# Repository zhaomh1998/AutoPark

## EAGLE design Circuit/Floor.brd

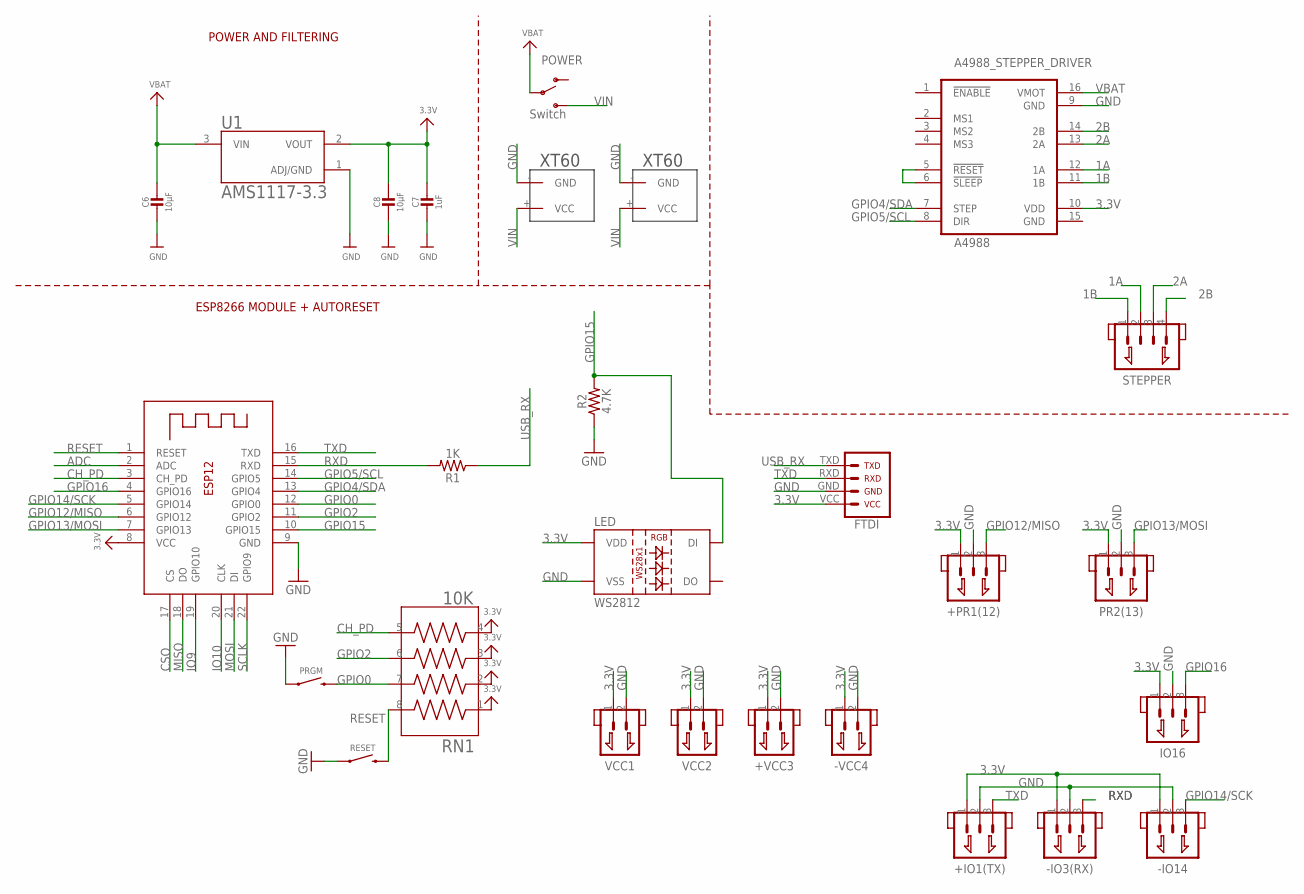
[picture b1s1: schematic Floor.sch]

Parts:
+IO1(TX): XH_2.54_3P; XH2.54_3P
+PR1(12): XH_2.54_3P; XH2.54_3P
+VCC3: XH_2.54_2P; XH2.54_2P
-IO3(RX), -IO14: XH_2.54_3P; XH2.54_3P
-VCC4: XH_2.54_2P; XH2.54_2P
A4988: A4988_STEPPER_DRIVER; A4988
C6, C8: 10µF; MICROBUILDER__0805
C7: 1uF; MICROBUILDER__0603
IO16: XH_2.54_3P; XH2.54_3P
LED: WS2812; LED-TRICOLOR-5050-IC
POWER: Switch; SWITCH_SPDT_PTH_11.6X4.0MM
PR2(13): XH_2.54_3P; XH2.54_3P
PRGM: PUSHBUTTON; TACTILE_SWITCH_SMD_6.0X3.5MM
R1: 1K; 1206
R2: 4.7K; 1206
RESET: PUSHBUTTON; TACTILE_SWITCH_SMD_6.0X3.5MM
RN1: 10K; RESCAF80P320X160X60-8N
STEPPER: XH_2.54_4P; XH2.54_4P
U1: AMS1117-3.3; SOT229P700X180-4N
U$7, U$9: XT60
U$11: FTDI; 1X06
VCC1, VCC2: XH_2.54_2P; XH2.54_2P
X2: ESP-12; MICROBUILDER_ESP-12E

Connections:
1A: A4988.12 (1A), STEPPER.2
1B: A4988.11 (1B), STEPPER.1
2A: A4988.13 (2A), STEPPER.3
2B: A4988.14 (2B), STEPPER.4
3.3V: +IO1(TX).1, +PR1(12).1, +VCC3.1, -IO3(RX).1, -IO14.1, -VCC4.1, A4988.10 (VDD), C7.1, C8.1, IO16.1, LED.VDD, PR2(13).1, RN1.1, RN1.2, RN1.3, RN1.4, U1.2 (VOUT), U$11.VCC, VCC1.1, VCC2.1, X2.8 (VCC)
ADC: X2.2 (ADC)
CH_PD: RN1.5, X2.3 (CH_PD)
CSO: X2.17 (CS)
GND: +IO1(TX).2, +PR1(12).2, +VCC3.2, -IO3(RX).2, -IO14.2, -VCC4.2, A4988.9 (GND), A4988.15 (GND), C6.2, C7.2, C8.2, IO16.2, LED.VSS, PR2(13).2, PRGM.1, R2.1, RESET.1, U1.1 (ADJ/GND), U$7.- (GND), U$9.- (GND), U$11.GND, VCC1.2, VCC2.2, X2.9 (GND)
GPIO0: PRGM.2, RN1.7, X2.12 (GPIO0)
GPIO2: RN1.6, X2.11 (GPIO2)
GPIO4/SDA: A4988.7 (STEP), X2.13 (GPIO4)
GPIO5/SCL: A4988.8 (DIR), X2.14 (GPIO5)
GPIO12/MISO: +PR1(12).3, X2.6 (GPIO12)
GPIO13/MOSI: PR2(13).3, X2.7 (GPIO13)
GPIO14/SCK: -IO14.3, X2.5 (GPIO14)
GPIO15: LED.DIN (DI), R2.2, X2.10 (GPIO15)
GPIO16: IO16.3, X2.4 (GPIO16)
IO9: X2.19 (GPIO10)
IO10: X2.20 (CLK)
MISO: X2.18 (DO)
MOSI: X2.21 (DI)
unnamed: A4988.5 (!RESET), A4988.6 (!SLEEP)
RESET: RESET.2, RN1.8, X2.1 (RESET)
RXD: -IO3(RX).3, R1.2, X2.15 (RXD)
SCLK: X2.22 (GPIO9)
TXD: +IO1(TX).3, U$11.RXD, X2.16 (TXD)
USB_RX: R1.1, U$11.TXD
VBAT: A4988.16 (VMOT), C6.1, POWER.2, U1.3 (VIN)
VIN: POWER.3 (S), U$7.+ (VCC), U$9.+ (VCC)

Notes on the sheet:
POWER AND FILTERING
ESP8266 MODULE + AUTORESET

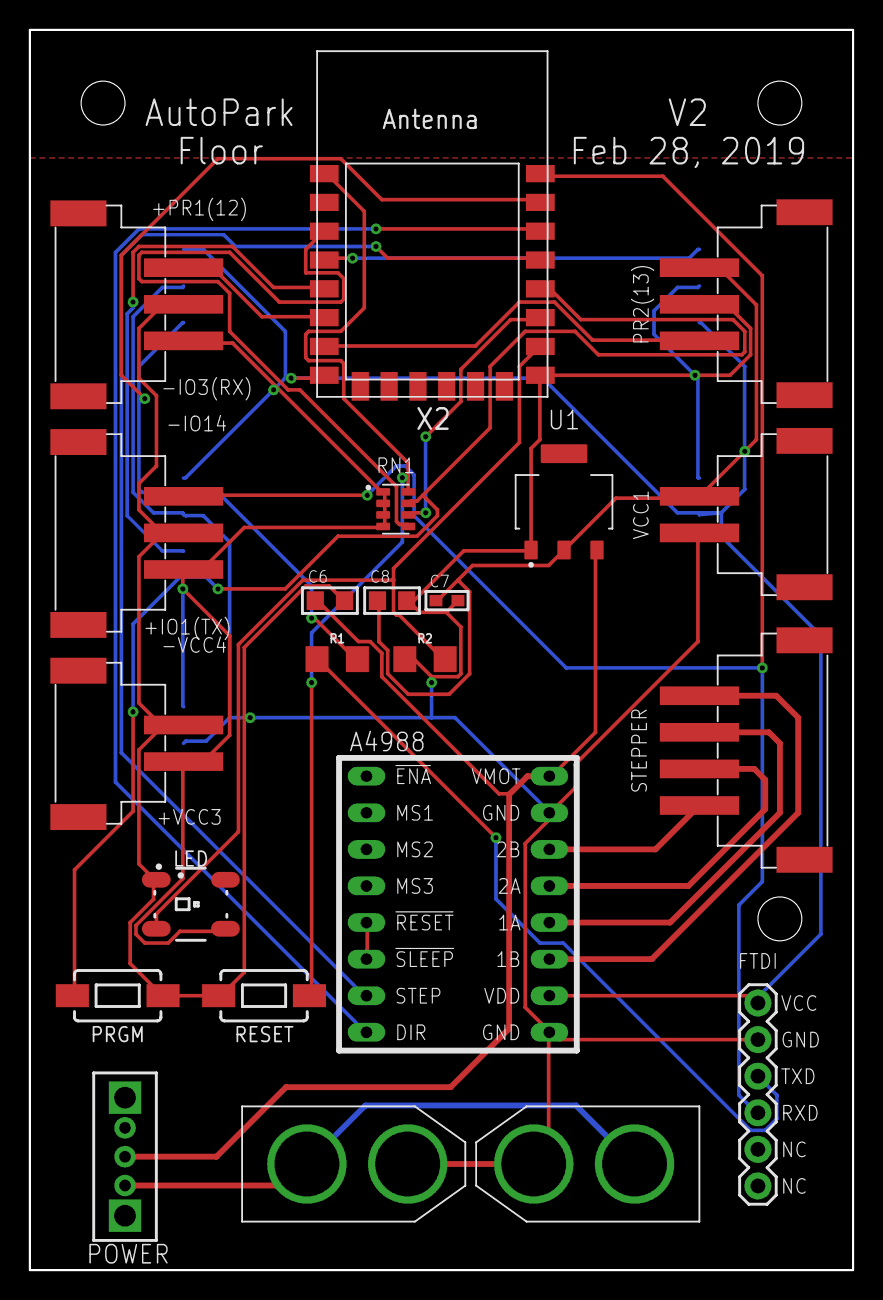
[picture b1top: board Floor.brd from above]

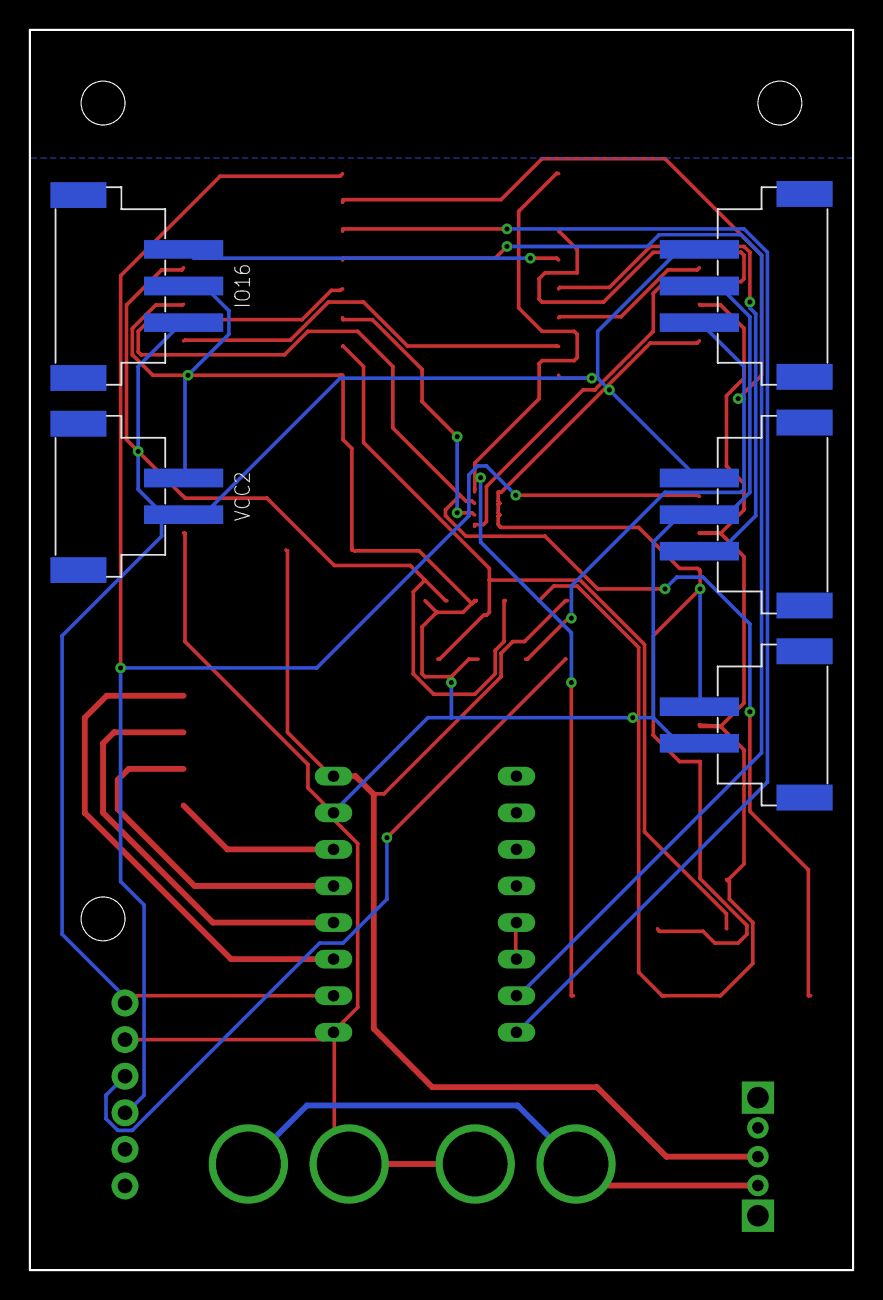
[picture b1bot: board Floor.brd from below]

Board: 2 copper layers, 57.2 x 86.1 mm, 27 parts (5 on the bottom side), 23 nets.

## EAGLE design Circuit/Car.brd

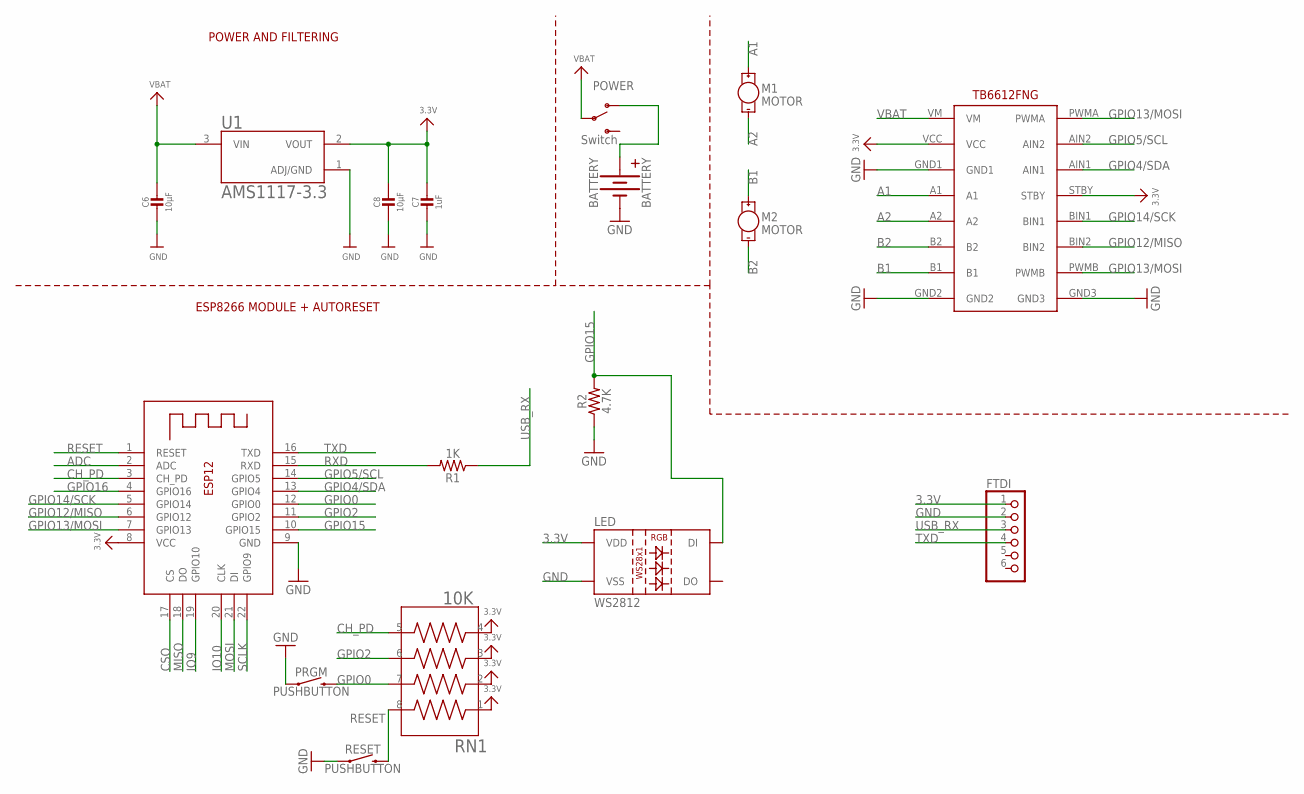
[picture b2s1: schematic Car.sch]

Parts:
BATTERY: BATTERY; BATTERY-AA-KIT
C6, C8: 10µF; MICROBUILDER__0805
C7: 1uF; MICROBUILDER__0603
FTDI: PINHD-1X6; 1X06
LED: WS2812; LED-TRICOLOR-5050-IC
M1, M2: MOTOR; 1X02_PLUS_MINUS
POWER: Switch; SWITCH_SPDT_PTH_11.6X4.0MM
PRGM: PUSHBUTTON; TACTILE_SWITCH_SMD_6.0X3.5MM
R1: 1K; 1206
R2: 4.7K; 1206
RESET: PUSHBUTTON; TACTILE_SWITCH_SMD_6.0X3.5MM
RN1: 10K; RESCAF80P320X160X60-8N
TB1: TB6612FNG
U1: AMS1117-3.3; SOT229P700X180-4N
X2: ESP-12; ESP-12E

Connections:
3.3V: C7.1, C8.1, FTDI.1, LED.VDD, RN1.1, RN1.2, RN1.3, RN1.4, TB1.STBY, TB1.VCC, U1.2 (VOUT), X2.8 (VCC)
A1: M1.+, TB1.A1
A2: M1.-, TB1.A2
ADC: X2.2 (ADC)
B1: M2.+, TB1.B1
B2: M2.-, TB1.B2
CH_PD: RN1.5, X2.3 (CH_PD)
CSO: X2.17 (CS)
GND: BATTERY.GND (-), C6.2, C7.2, C8.2, FTDI.2, LED.VSS, PRGM.1, R2.1, RESET.1, TB1.GND1, TB1.GND2, TB1.GND3, U1.1 (ADJ/GND), X2.9 (GND)
GPIO0: PRGM.2, RN1.7, X2.12 (GPIO0)
GPIO2: RN1.6, X2.11 (GPIO2)
GPIO4/SDA: TB1.AIN1, X2.13 (GPIO4)
GPIO5/SCL: TB1.AIN2, X2.14 (GPIO5)
GPIO12/MISO: TB1.BIN2, X2.6 (GPIO12)
GPIO13/MOSI: TB1.PWMA, TB1.PWMB, X2.7 (GPIO13)
GPIO14/SCK: TB1.BIN1, X2.5 (GPIO14)
GPIO15: LED.DIN (DI), R2.2, X2.10 (GPIO15)
GPIO16: X2.4 (GPIO16)
IO9: X2.19 (GPIO10)
IO10: X2.20 (CLK)
MISO: X2.18 (DO)
MOSI: X2.21 (DI)
unnamed: BATTERY.PWR (+), POWER.1 (O)
RESET: RESET.2, RN1.8, X2.1 (RESET)
RXD: R1.2, X2.15 (RXD)
SCLK: X2.22 (GPIO9)
TXD: FTDI.4, X2.16 (TXD)
USB_RX: FTDI.3, R1.1
VBAT: C6.1, POWER.2, TB1.VM, U1.3 (VIN)

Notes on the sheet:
POWER AND FILTERING
ESP8266 MODULE + AUTORESET

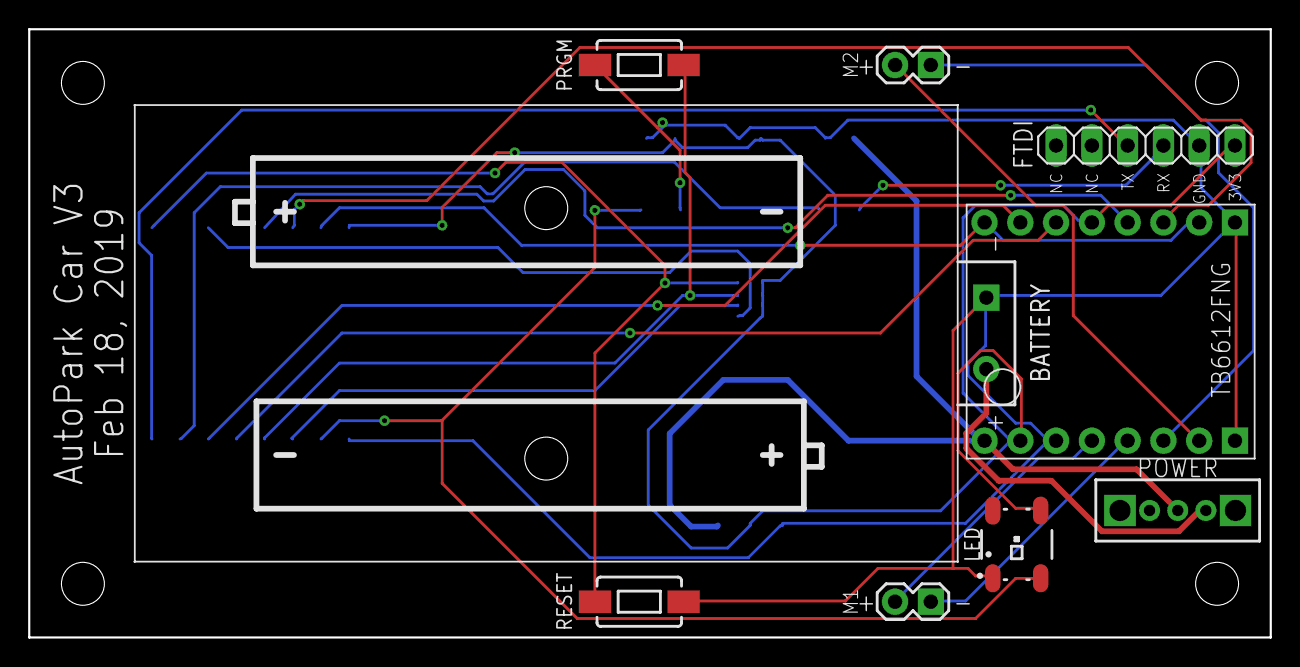
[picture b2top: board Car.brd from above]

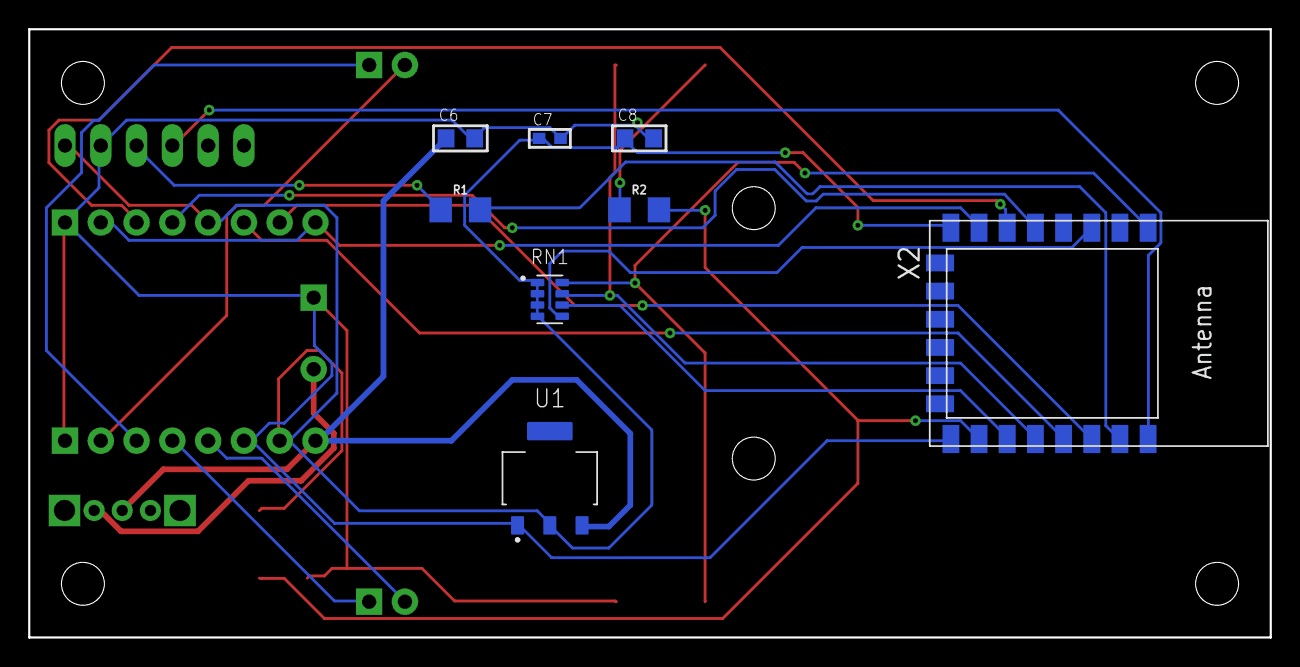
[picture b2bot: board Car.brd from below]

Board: 2 copper layers, 88.1 x 43.2 mm, 17 parts (8 on the bottom side), 21 nets.

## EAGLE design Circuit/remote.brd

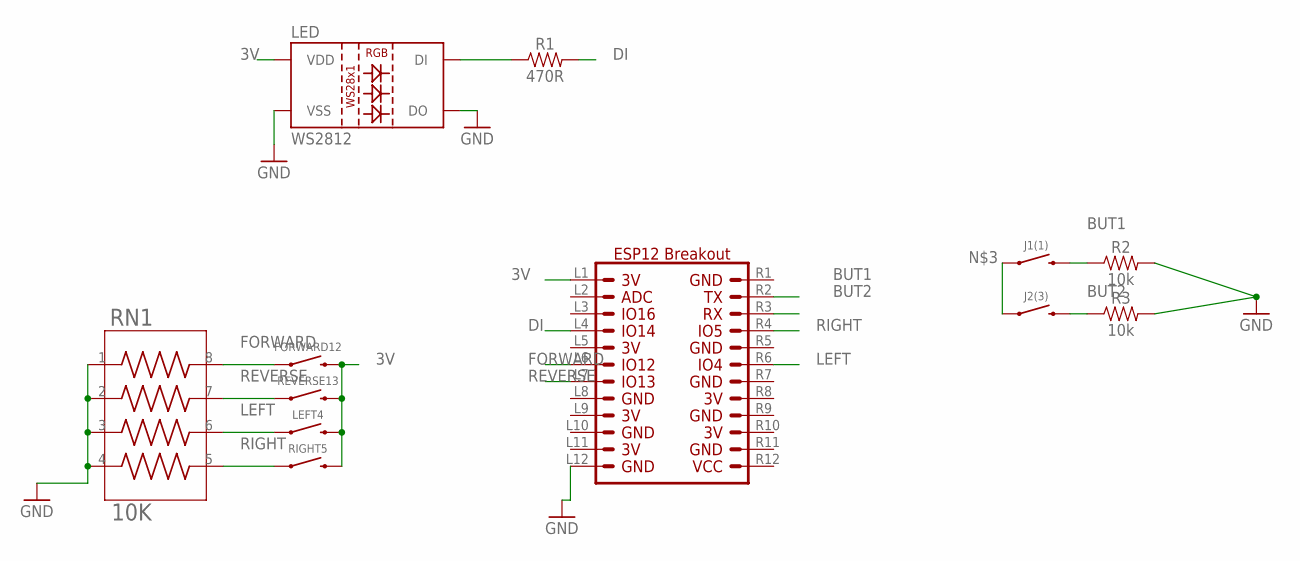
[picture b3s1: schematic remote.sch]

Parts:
FORWARD12: PUSHBUTTON_THD; TACTILE_SWITCH_PTH_6.0MM
J1(1), J2(3): PUSHBUTTON_THD; TACTILE_SWITCH_PTH_6.0MM
LED: WS2812; LED-TRICOLOR-5050-IC
LEFT4: PUSHBUTTON_THD; TACTILE_SWITCH_PTH_6.0MM
R1: 470R; SPARKFUN-RESISTORS_1206
R2, R3: 10k; SPARKFUN-RESISTORS_1206
REVERSE13: PUSHBUTTON_THD; TACTILE_SWITCH_PTH_6.0MM
RIGHT5: PUSHBUTTON_THD; TACTILE_SWITCH_PTH_6.0MM
RN1: 10K; RESCAF80P320X160X60-8N
U$1: ESP12_BREAKOUT; ESP12_BREAKOUT_CONN

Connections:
3V: FORWARD12.3 (2), LED.VDD, LEFT4.3 (2), REVERSE13.3 (2), RIGHT5.3 (2), U$1.L1
BUT1: J1(1).3 (2), R2.1, U$1.R2
BUT2: J2(3).3 (2), R3.1, U$1.R3
DI: R1.2, U$1.L4
FORWARD: FORWARD12.1, RN1.8, U$1.L6
GND: LED.DOUT (DO), LED.VSS, R2.2, R3.2, RN1.1, RN1.2, RN1.3, RN1.4, U$1.L12
LEFT: LEFT4.1, RN1.6, U$1.R6
unnamed: J1(1).1, J2(3).1
unnamed: LED.DIN (DI), R1.1
REVERSE: REVERSE13.1, RN1.7, U$1.L7
RIGHT: RIGHT5.1, RN1.5, U$1.R4

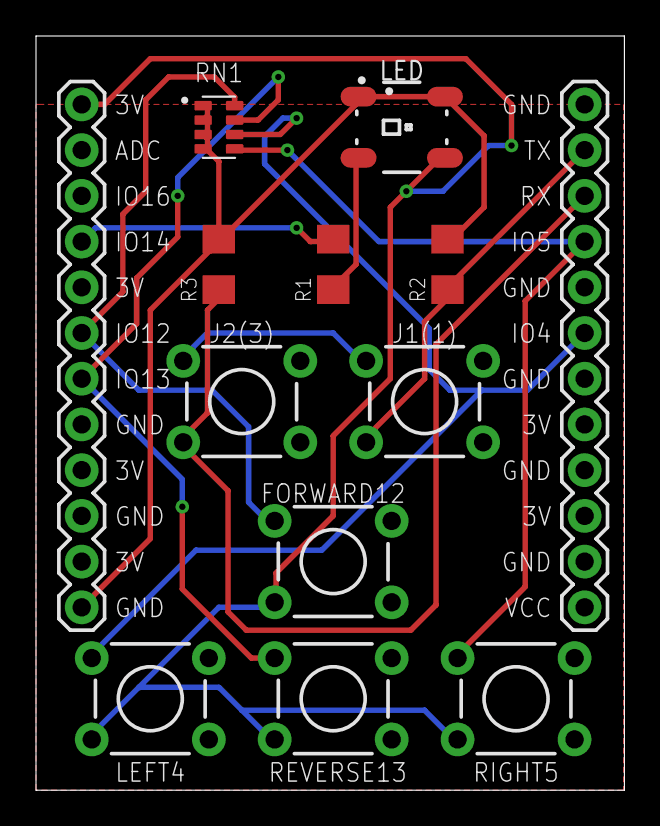
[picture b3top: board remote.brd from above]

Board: 2 copper layers, 32.7 x 41.9 mm, 12 parts (0 on the bottom side), 11 nets.

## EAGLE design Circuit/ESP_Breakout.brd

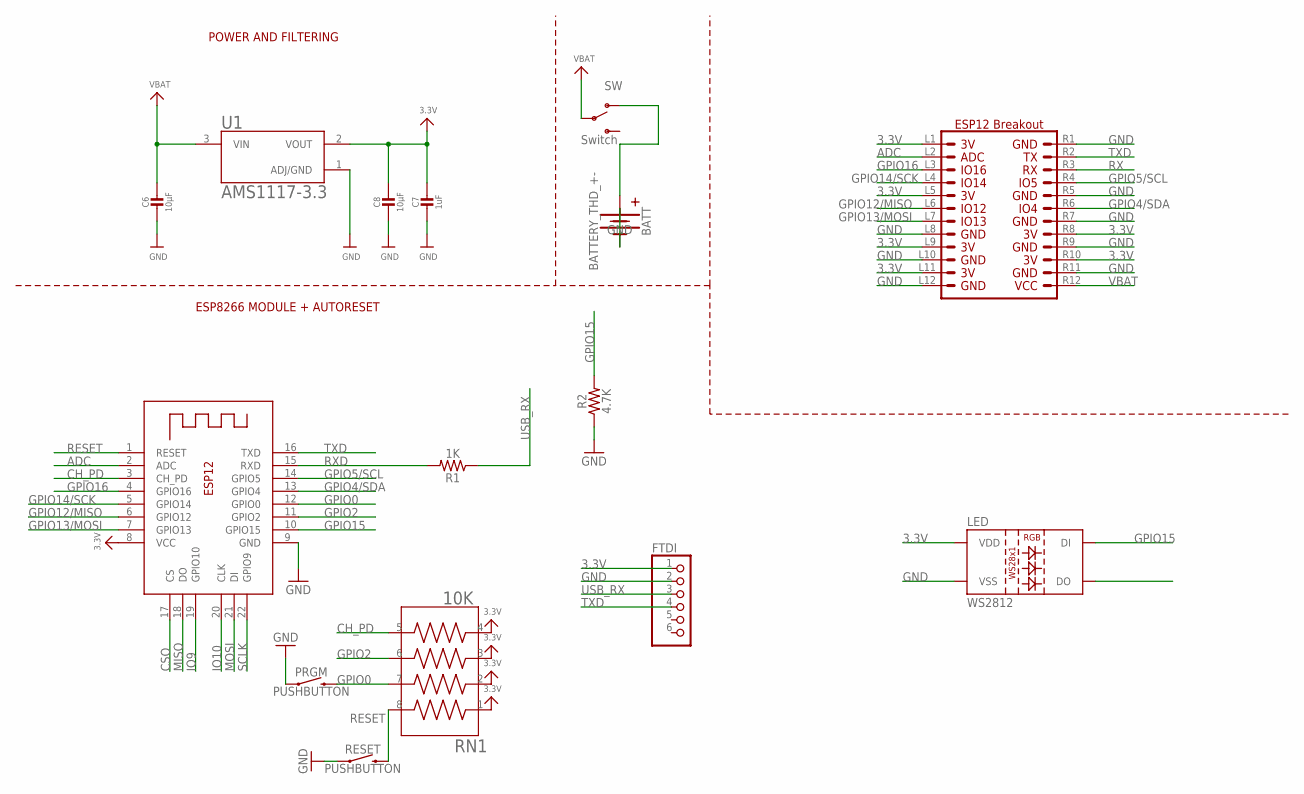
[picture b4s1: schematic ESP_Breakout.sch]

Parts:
BATT: BATTERY_THD_+-; 1X02_PLUS_MINUS
C6, C8: 10µF; MICROBUILDER__0805
C7: 1uF; MICROBUILDER__0603
FTDI: PINHD-1X6; 1X06
LED: WS2812; LED-TRICOLOR-5050-IC
PRGM: PUSHBUTTON; TACTILE_SWITCH_SMD_6.0X3.5MM
R1: 1K; 1206
R2: 4.7K; 1206
RESET: PUSHBUTTON; TACTILE_SWITCH_SMD_6.0X3.5MM
RN1: 10K; RESCAF80P320X160X60-8N
SW: Switch; SWITCH_SPDT_PTH_11.6X4.0MM
U1: AMS1117-3.3; SOT229P700X180-4N
U$7: ESP12_BREAKOUT; ESP12_BREAKOUT_CONN
X2: ESP-12; ESP-12E

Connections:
3.3V: C7.1, C8.1, FTDI.1, LED.VDD, RN1.1, RN1.2, RN1.3, RN1.4, U1.2 (VOUT), U$7.L1, U$7.L5, U$7.L9, U$7.L11, U$7.R8, U$7.R10, X2.8 (VCC)
ADC: U$7.L2, X2.2 (ADC)
CH_PD: RN1.5, X2.3 (CH_PD)
CSO: X2.17 (CS)
GND: BATT.-, C6.2, C7.2, C8.2, FTDI.2, LED.VSS, PRGM.1, R2.1, RESET.1, U1.1 (ADJ/GND), U$7.L8, U$7.L10, U$7.L12, U$7.R1, U$7.R5, U$7.R7, U$7.R9, U$7.R11, X2.9 (GND)
GPIO0: PRGM.2, RN1.7, X2.12 (GPIO0)
GPIO2: RN1.6, X2.11 (GPIO2)
GPIO4/SDA: U$7.R6, X2.13 (GPIO4)
GPIO5/SCL: U$7.R4, X2.14 (GPIO5)
GPIO12/MISO: U$7.L6, X2.6 (GPIO12)
GPIO13/MOSI: U$7.L7, X2.7 (GPIO13)
GPIO14/SCK: U$7.L4, X2.5 (GPIO14)
GPIO15: LED.DIN (DI), R2.2, X2.10 (GPIO15)
GPIO16: U$7.L3, X2.4 (GPIO16)
IO9: X2.19 (GPIO10)
IO10: X2.20 (CLK)
MISO: X2.18 (DO)
MOSI: X2.21 (DI)
unnamed: BATT.+, SW.1 (O)
RESET: RESET.2, RN1.8, X2.1 (RESET)
RX: U$7.R3
RXD: R1.2, X2.15 (RXD)
SCLK: X2.22 (GPIO9)
TXD: FTDI.4, U$7.R2, X2.16 (TXD)
USB_RX: FTDI.3, R1.1
VBAT: C6.1, SW.2, U1.3 (VIN), U$7.R12

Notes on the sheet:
POWER AND FILTERING
ESP8266 MODULE + AUTORESET

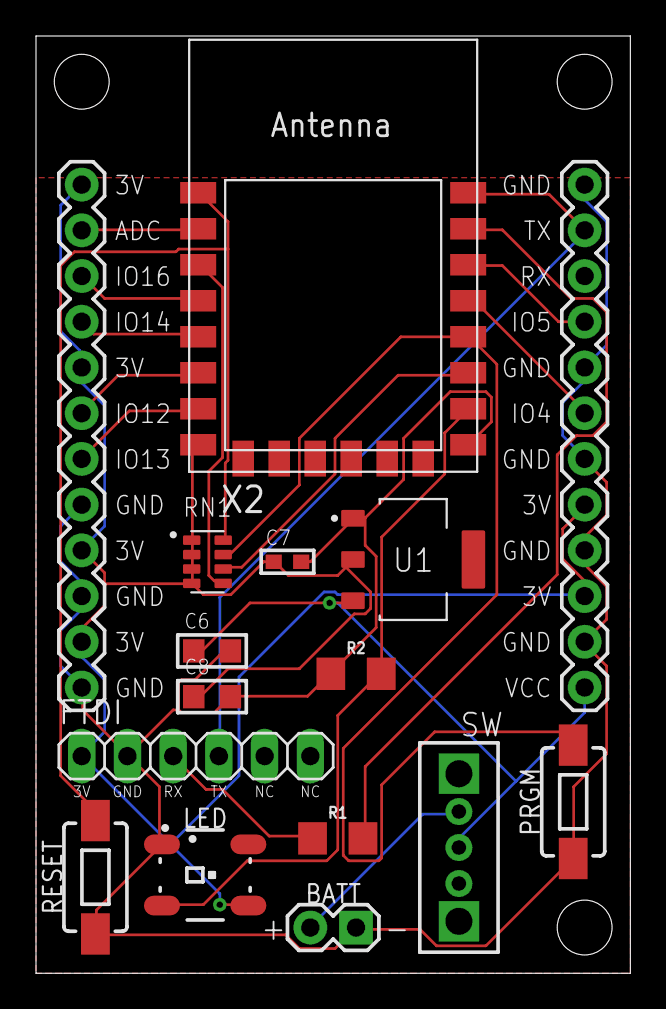
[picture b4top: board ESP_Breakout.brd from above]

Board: 2 copper layers, 33.0 x 52.1 mm, 15 parts (0 on the bottom side), 19 nets.

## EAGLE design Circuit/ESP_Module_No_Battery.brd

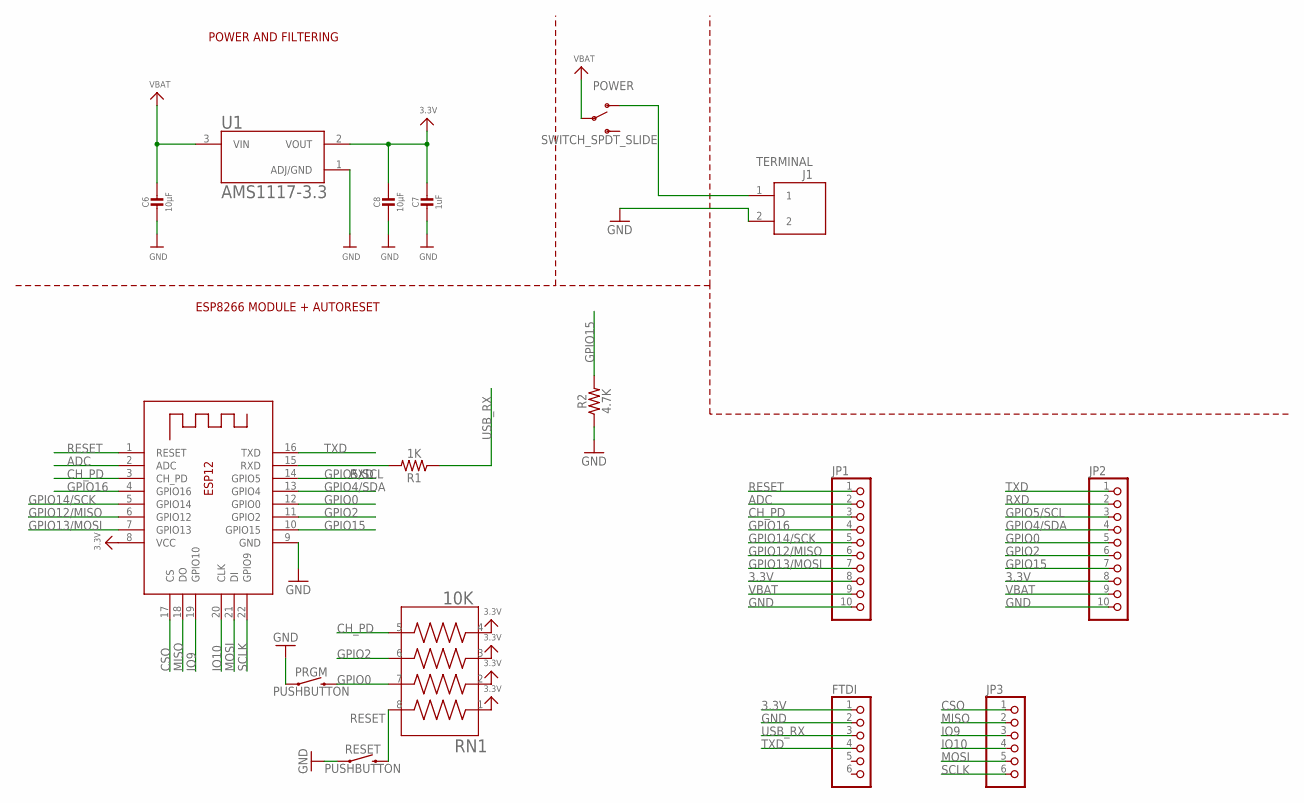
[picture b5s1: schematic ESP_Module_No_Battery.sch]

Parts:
C6, C8: 10µF; 0805-NO
C7: 1uF; 0603-NO
FTDI: PINHD-1X6; 1X06
J1: TERMINAL; ED555/2DS
JP1, JP2: PINHD-1X10; 1X10
JP3: PINHD-1X6; 1X06
POWER: SWITCH_SPDT_SLIDE; SWITCH_SPDT_PTH_11.6X4.0MM
PRGM: PUSHBUTTON; TACTILE_SWITCH_SMD_6.0X3.5MM
R1: 1K; 1206
R2: 4.7K; 1206
RESET: PUSHBUTTON; TACTILE_SWITCH_SMD_6.0X3.5MM
RN1: 10K; RESCAF80P320X160X60-8N
U1: AMS1117-3.3; SOT229P700X180-4N
X2: ESP-12; ESP-12E

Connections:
3.3V: C7.1, C8.1, FTDI.1, JP1.8, JP2.8, RN1.1, RN1.2, RN1.3, RN1.4, U1.2 (VOUT), X2.8 (VCC)
ADC: JP1.2, X2.2 (ADC)
CH_PD: JP1.3, RN1.5, X2.3 (CH_PD)
CSO: JP3.1, X2.17 (CS)
GND: C6.2, C7.2, C8.2, FTDI.2, J1.2, JP1.10, JP2.10, PRGM.1, R2.1, RESET.1, U1.1 (ADJ/GND), X2.9 (GND)
GPIO0: JP2.5, PRGM.2, RN1.7, X2.12 (GPIO0)
GPIO2: JP2.6, RN1.6, X2.11 (GPIO2)
GPIO4/SDA: JP2.4, X2.13 (GPIO4)
GPIO5/SCL: JP2.3, X2.14 (GPIO5)
GPIO12/MISO: JP1.6, X2.6 (GPIO12)
GPIO13/MOSI: JP1.7, X2.7 (GPIO13)
GPIO14/SCK: JP1.5, X2.5 (GPIO14)
GPIO15: JP2.7, R2.2, X2.10 (GPIO15)
GPIO16: JP1.4, X2.4 (GPIO16)
IO9: JP3.3, X2.19 (GPIO10)
IO10: JP3.4, X2.20 (CLK)
MISO: JP3.2, X2.18 (DO)
MOSI: JP3.5, X2.21 (DI)
unnamed: J1.1, POWER.1 (O)
RESET: JP1.1, RESET.2, RN1.8, X2.1 (RESET)
RXD: JP2.2, R1.2, X2.15 (RXD)
SCLK: JP3.6, X2.22 (GPIO9)
TXD: FTDI.4, JP2.1, X2.16 (TXD)
USB_RX: FTDI.3, R1.1
VBAT: C6.1, JP1.9, JP2.9, POWER.2, U1.3 (VIN)

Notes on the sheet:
POWER AND FILTERING
ESP8266 MODULE + AUTORESET

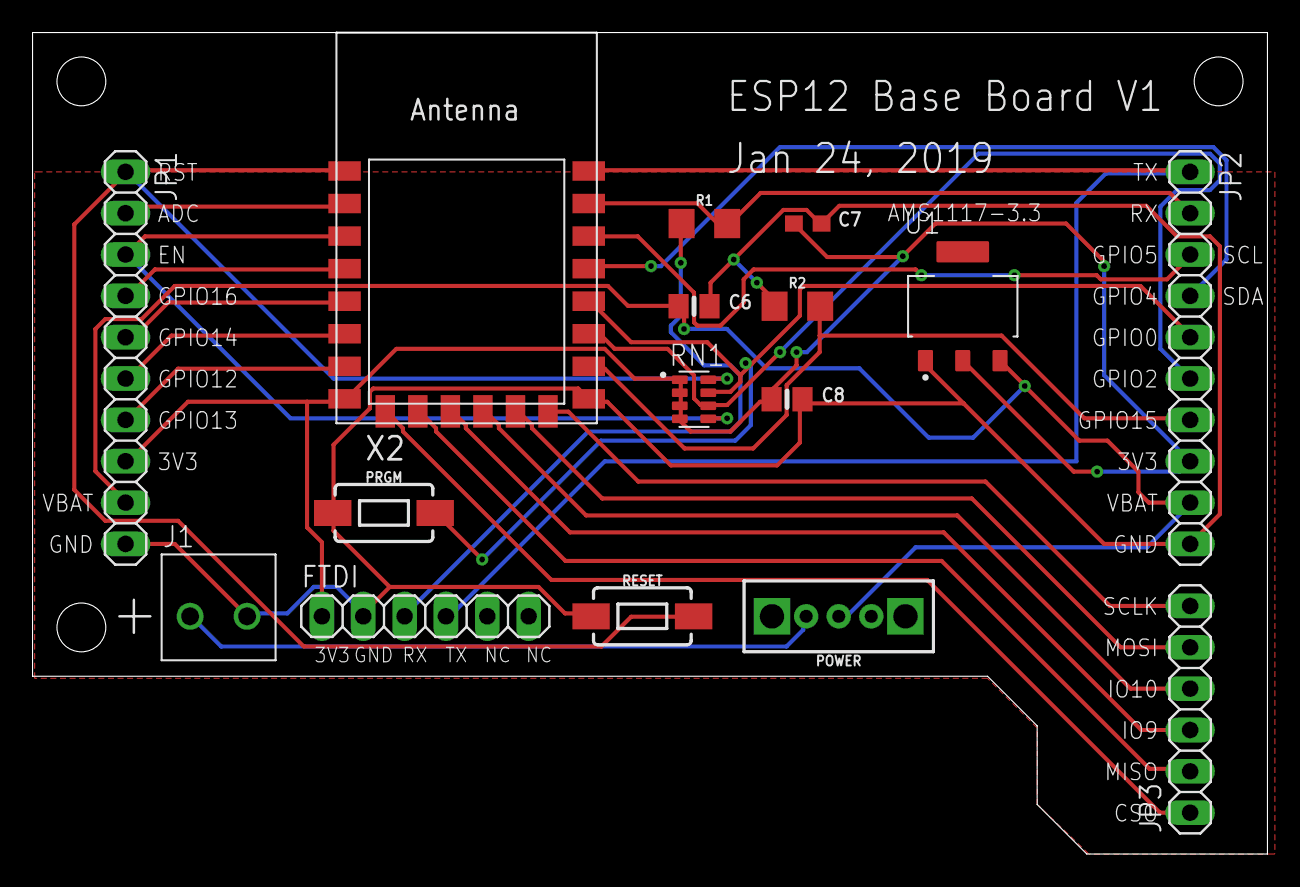
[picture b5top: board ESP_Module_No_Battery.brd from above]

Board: 2 copper layers, 75.9 x 50.5 mm, 16 parts (0 on the bottom side), 25 nets.

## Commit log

2019-01-16 ESPNow initial test
2019-01-18 Implement direct messaging
2019-01-19 Remote car v1 implementation
2019-01-22 add eagle library
2019-01-23 esp module schematics
2019-01-23 init cad design, schematics update
2019-01-24 ESP Module V1
2019-01-28 changed elevator base and shaft
2019-01-28 changed assembly
2019-01-28 Update assembly
2019-01-28 add screenshots
2019-02-03 Solidworks V1 floor
2019-02-04 Add floor assembly, extend slide dimension
2019-02-04 v1 final cad
2019-02-05 Update remote controller software
2019-02-05 Floor CAD revamp
2019-02-13 library update, new car sch with motor driver
2019-02-13 add elevator
2019-02-14 Use one output for both pwms
2019-02-14 update library, car PCB V2
2019-02-18 updated slide
2019-02-18 added additional part for slide
2019-02-18 eagle library update, code repo restructure
2019-02-18 add remote button shield
2019-02-18 ESP Breakout and remote shield pcb
2019-02-19 car v3 with RGB, update platformio ESP dev structure
2019-02-19 ESPNow base class; ESPNow tests; refactor
2019-02-20 eagle library add connectors
2019-02-20 floor pcb v0
2019-02-22 esp master code
2019-02-24 master slave espnow classes
2019-02-27 add stepper
2019-02-28 correct flipped xh conns
2019-03-01 floor pcb, led library, espnow wip
2019-03-01 refactor, bug fix
2019-03-02 bug fix
2019-03-02 refactor
2019-03-02 update base class
2019-03-02 debug wip
2019-03-03 bug fix, car working
2019-03-03 Update logger
2019-03-03 push before restructure command handling strategy
2019-03-03 new message callback strategy implementation
2019-03-03 Floor class prototype
2019-03-04 debugger implementation, clean up repo
2019-03-04 car multiple master; floor park in lot implementation
2019-03-05 debugger bug fix, UART command processor implementation
2019-03-05 command sets def
2019-03-05 Floor command processor
2019-03-05 Command set refactor, floor stepper implementation
2019-03-06 bug fix, new command set integration
2019-03-07 bug fix for ESPNow command handler buffer
2019-03-07 bug fix for park into lot
2019-03-07 master command handler implementation
2019-03-07 clean up; new stepper controlling structure
2019-03-07 master stepper control bug fix
2019-03-07 stepper implementation
2019-03-08 Finalize mainESP
2019-03-08 Disable serial.print
2019-03-08 final turning
2019-03-13 new cart offset, finalize

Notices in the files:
parts and their libraries:
microbuilder: This work is placed in the public domain, and may be freely used for commercial and non-commercial work with the following conditions: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
SparkFun-Resistors: Licensing: Creative Commons ShareAlike 4.0 International - https://creativecommons.org/licenses/by-sa/4.0
